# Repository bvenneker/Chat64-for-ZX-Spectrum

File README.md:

# Chat64 for ZX Spectrum
 The chat64 cartridge, but for zx spectrum!

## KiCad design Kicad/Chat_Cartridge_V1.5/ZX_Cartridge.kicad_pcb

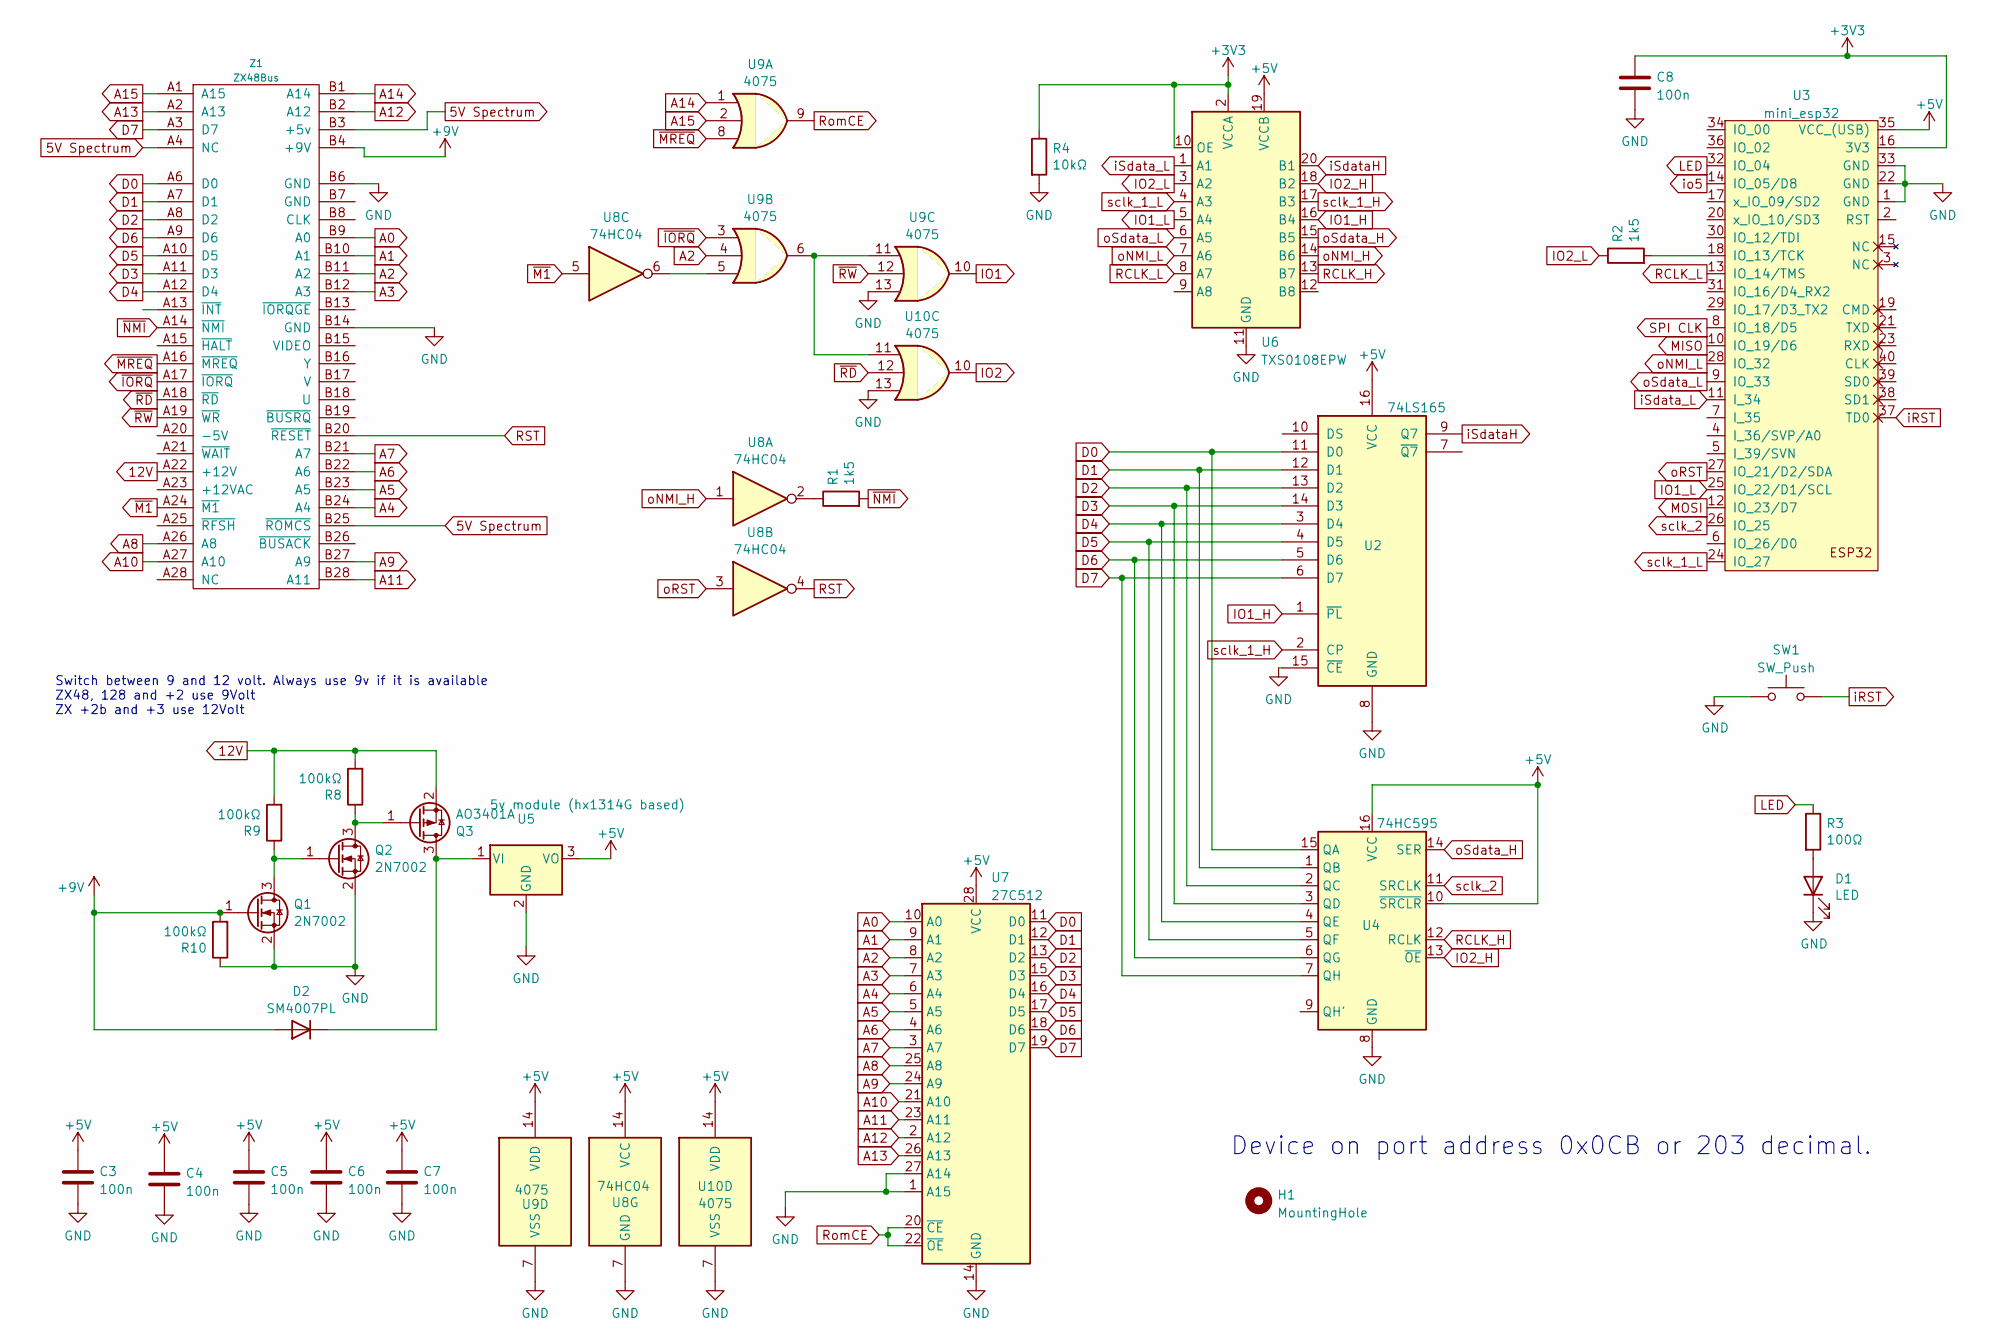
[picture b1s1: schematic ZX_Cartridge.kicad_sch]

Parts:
C3, C4, C5, C6, C7, C8: 100n; C_0402_1005Metric
D1: LED; LED_0603_1608Metric
D2: SM4007PL; D_SOD-123F
H1: MountingHole; MountingHole_3.2mm_M3
Q1, Q2: 2N7002; SOT-23
Q3: AO3401A; SOT-23
R1, R2: 1k5; R_0402_1005Metric
R3: 100Ω; R_0402_1005Metric
R4: 10kΩ; R_0402_1005Metric
R8, R9, R10: 100kΩ; R_0402_1005Metric
SW1: SW_Push; SW_PUSH_HALF_6mm
U2: 74LS165; SOIC-16_3.9x9.9mm_P1.27mm
U3: mini_esp32; ESP32_mini
U4: 74HC595; SOIC-16_3.9x9.9mm_P1.27mm
U5: 5v module (hx1314G based); 5v_switching_TO220
U6: TXS0108EPW; TSSOP-20_4.4x6.5mm_P0.65mm
U7: 27C512; DIP-28_W15.24mm_Socket_LongPads
U8: 74HC04; SOIC-14_3.9x8.7mm_P1.27mm
U9, U10: 4075; SOIC-14_3.9x8.7mm_P1.27mm
Z1: ZX48Bus; ZX_Bus_Edge_Connector

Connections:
5V Spectrum: Z1.A4 (NC), Z1.B3 (+5v), Z1.B25 (~ROMCS)
12V: Q3.2 (S), R8.2, R9.2, Z1.A22 (+12V)
+3V3: C8.1, R4.1, U3.16 (3V3), U6.2 (VCCA), U6.10 (OE)
+5V: C3.1, C4.1, C5.1, C6.1, C7.1, U2.16 (VCC), U3.35 (VCC_(USB)), U4.10 (~SRCLR), U4.16 (VCC), U5.3 (VO), U6.19 (VCCB), U7.28 (VCC), U8.14 (VCC), U9.14 (VDD), U10.14 (VDD)
+9V: D2.2 (A), Q1.1 (G), R10.2, Z1.B4 (+9V)
A0: U7.10 (A0), Z1.B9 (A0)
A1: U7.9 (A1), Z1.B10 (A1)
A2: U7.8 (A2), U9.4, Z1.B11 (A2)
A3: U7.7 (A3), Z1.B12 (A3)
A4: U7.6 (A4), Z1.B24 (A4)
A5: U7.5 (A5), Z1.B23 (A5)
A6: U7.4 (A6), Z1.B22 (A6)
A7: U7.3 (A7), Z1.B21 (A7)
A8: U7.25 (A8), Z1.A26 (A8)
A9: U7.24 (A9), Z1.B27 (A9)
A10: U7.21 (A10), Z1.A27 (A10)
A11: U7.23 (A11), Z1.B28 (A11)
A12: U7.2 (A12), Z1.B2 (A12)
A13: U7.26 (A13), Z1.A2 (A13)
A14: U9.1, Z1.B1 (A14)
A15: U9.2, Z1.A1 (A15)
D0: U2.11 (D0), U4.15 (QA), U7.11 (D0), Z1.A6 (D0)
D1: U2.12 (D1), U4.1 (QB), U7.12 (D1), Z1.A7 (D1)
D2: U2.13 (D2), U4.2 (QC), U7.13 (D2), Z1.A8 (D2)
D3: U2.14 (D3), U4.3 (QD), U7.15 (D3), Z1.A11 (D3)
D4: U2.3 (D4), U4.4 (QE), U7.16 (D4), Z1.A12 (D4)
D5: U2.4 (D5), U4.5 (QF), U7.17 (D5), Z1.A10 (D5)
D6: U2.5 (D6), U4.6 (QG), U7.18 (D6), Z1.A9 (D6)
D7: U2.6 (D7), U4.7 (QH), U7.19 (D7), Z1.A3 (D7)
GND: C3.2, C4.2, C5.2, C6.2, C7.2, C8.2, D1.1 (K), Q1.2 (S), Q2.2 (S), R4.2, R10.1, SW1.1, U2.8 (GND), U2.15 (~CE), U3.1 (GND), U3.22 (GND), U3.33 (GND), U4.8 (GND), U5.2 (GND), U6.11 (GND), U7.1 (A15), U7.14 (GND), U7.27 (A14), U8.7 (GND), U9.7 (VSS), U9.13, U10.7 (VSS), U10.13, Z1.B6 (GND), Z1.B14 (GND)
IO1: U9.10
IO1_H: U2.1 (~PL), U6.16 (B4)
IO1_L: U3.25 (IO_22/D1/SCL), U6.5 (A4)
IO2: U10.10
IO2_H: U4.13 (~OE), U6.18 (B2)
IO2_L: R2.1, U6.3 (A2)
LED: R3.1, U3.32 (IO_04)
MISO: U3.10 (IO_19/D6)
MOSI: U3.12 (IO_23/D7)
unnamed: D1.2 (A), R3.2
unnamed: D2.1 (K), Q3.3 (D), U5.1 (VI)
unnamed: Q1.3 (D), Q2.1 (G), R9.1
unnamed: Q2.3 (D), Q3.1 (G), R8.1
unnamed: R1.1, U8.2
unnamed: R2.2, U3.18 (IO_13/TCK)
unnamed: U8.6, U9.5
unnamed: U9.6, U9.11, U10.11
RCLK_H: U4.12 (RCLK), U6.13 (B7)
RCLK_L: U3.13 (IO_14/TMS), U6.8 (A7)
RST: U8.4, Z1.B20 (~RESET)
RomCE: U7.20 (~CE), U7.22 (~OE), U9.9
SPI CLK: U3.8 (IO_18/D5)
iRST: SW1.2, U3.37 (TD0)
iSdataH: U2.9 (Q7), U6.20 (B1)
iSdata_L: U3.11 (I_34), U6.1 (A1)
io5: U3.14 (IO_05/D8)
oNMI_H: U6.14 (B6), U8.1
oNMI_L: U3.28 (IO_32), U6.7 (A6)
oRST: U3.27 (IO_21/D2/SDA), U8.3
oSdata_H: U4.14 (SER), U6.15 (B5)
oSdata_L: U3.9 (IO_33), U6.6 (A5)
sclk_1_H: U2.2 (CP), U6.17 (B3)
sclk_1_L: U3.24 (IO_27), U6.4 (A3)
sclk_2: U3.26 (IO_25), U4.11 (SRCLK)
~IORQ: U9.3, Z1.A17 (~IORQ)
~M1: U8.5, Z1.A24 (~M1)
~MREQ: U9.8, Z1.A16 (~MREQ)
~NMI: R1.2, Z1.A14 (~NMI)
~RD: U10.12, Z1.A18 (~RD)
~RW: U9.12, Z1.A19 (~WR)

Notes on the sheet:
Device on port address 0x0CB or 203 decimal.
Switch between 9 and 12 volt. Always use 9v if it is available ZX48, 128 and +2 use 9Volt ZX +2b and +3 use 12Volt

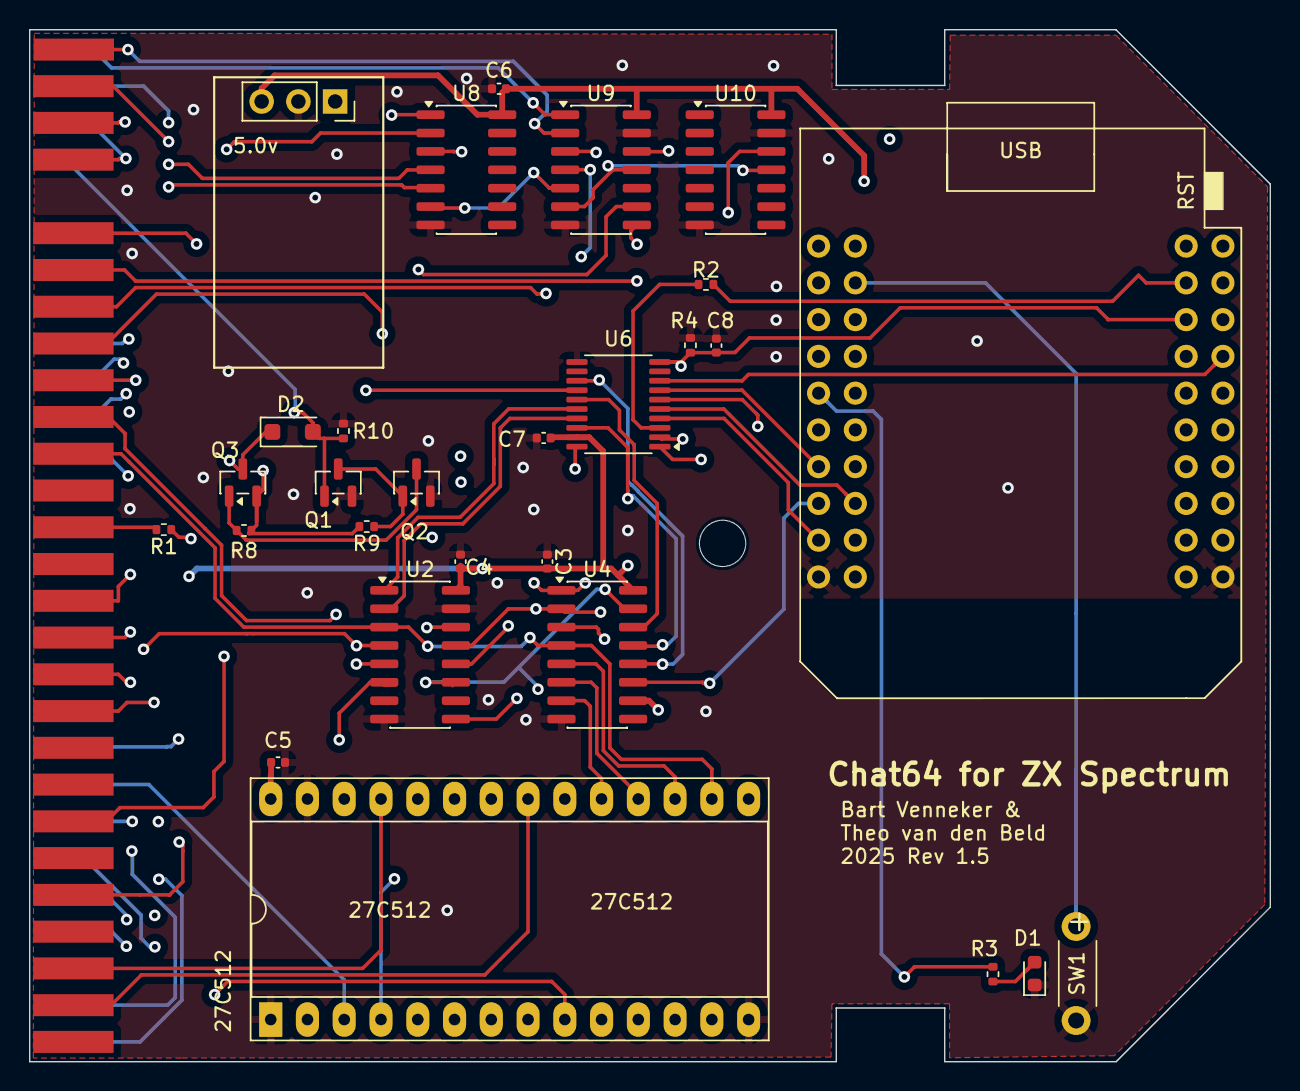
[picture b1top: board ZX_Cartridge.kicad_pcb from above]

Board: 4 copper layers, 85.7 x 71.3 mm, 30 parts (0 on the bottom side), 64 nets.

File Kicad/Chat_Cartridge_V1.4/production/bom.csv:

Designator,Footprint,Quantity,Value,LCSC Part #
"C3, C4, C5, C6, C7, C8",C_Disc_D6.0mm_W2.5mm_P5.00mm,6,100n,
D1,LED_D3.0mm,1,LED,
D2,D_DO-34_SOD68_P7.62mm_Horizontal,1,BAT86,
H1,MountingHole_3.2mm_M3,1,MountingHole,
"Q1, Q2",TO-92_Inline,2,2N7000,
Q3,SOT-223-3_TabPin2,1,Q_PMOS_GDS,
"R1, R2",R_Axial_DIN0204_L3.6mm_D1.6mm_P5.08mm_Horizontal,2,1k5,
"R10, R8, R9",R_Axial_DIN0204_L3.6mm_D1.6mm_P5.08mm_Horizontal,3,100kΩ,
R3,R_Axial_DIN0204_L3.6mm_D1.6mm_P5.08mm_Horizontal,1,100Ω,
U1,DIP-20_W7.62mm_Socket_LongPads,1,GAL16V8,
U2,DIP-16_W7.62mm_Socket_LongPads,1,74LS165,
U3,ESP32_mini,1,mini_esp32,
U4,DIP-16_W7.62mm_Socket_LongPads,1,74HC595,
U5,5v_switching_TO220,1,5v module (hx1314G based),
U7,DIP-28_W15.24mm_Socket_LongPads,1,27C512,
U9,DIP-14_W7.62mm_Socket_LongPads,1,74HCT125,
Z1,ZX_Bus_Edge_Connector,1,ZX48Bus,

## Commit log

2024-09-15 small updates
2024-10-07 Code Cleanup
    - code cleanup
    - added the first version of the cartridge enclosure
    - added the label design
2024-10-07 Create label SVG file
2024-10-28 fix urgent messages
2024-12-02 comments
2024-12-08 update decmber
2024-12-08 no empty messages
    fixed: You should not be able to send an empty message
2024-12-09 better scrolling on private screen
2024-12-20 empty message fix
2025-01-11 small change for the click sound
    Now we use the official keyboard click sound
2025-01-31 New PCB and code
    Small bug fixes in the code
2025-02-09 feb2025
2025-02-24 bugfix
2025-03-27 small update in setup
2025-05-24 servercode
2025-06-05 optimized setup procedure
2025-06-05 matrix check
2025-06-06 refactoring
2025-07-31 Update zxChat64.asm
    bit of clean up and refactoring
2025-07-31 Fix for Spectrum Next
2025-08-29 softreset
2025-09-03 small update
2025-10-13 updates prep for +3
2026-01-05 UrlEncode fix
2026-01-07 small things
2026-02-27 unstable
2026-03-07 kicad
2026-03-14 more users
2026-04-11 removed curly brackets
2026-04-11 removed curly brackets .
2026-04-17 prgfile
